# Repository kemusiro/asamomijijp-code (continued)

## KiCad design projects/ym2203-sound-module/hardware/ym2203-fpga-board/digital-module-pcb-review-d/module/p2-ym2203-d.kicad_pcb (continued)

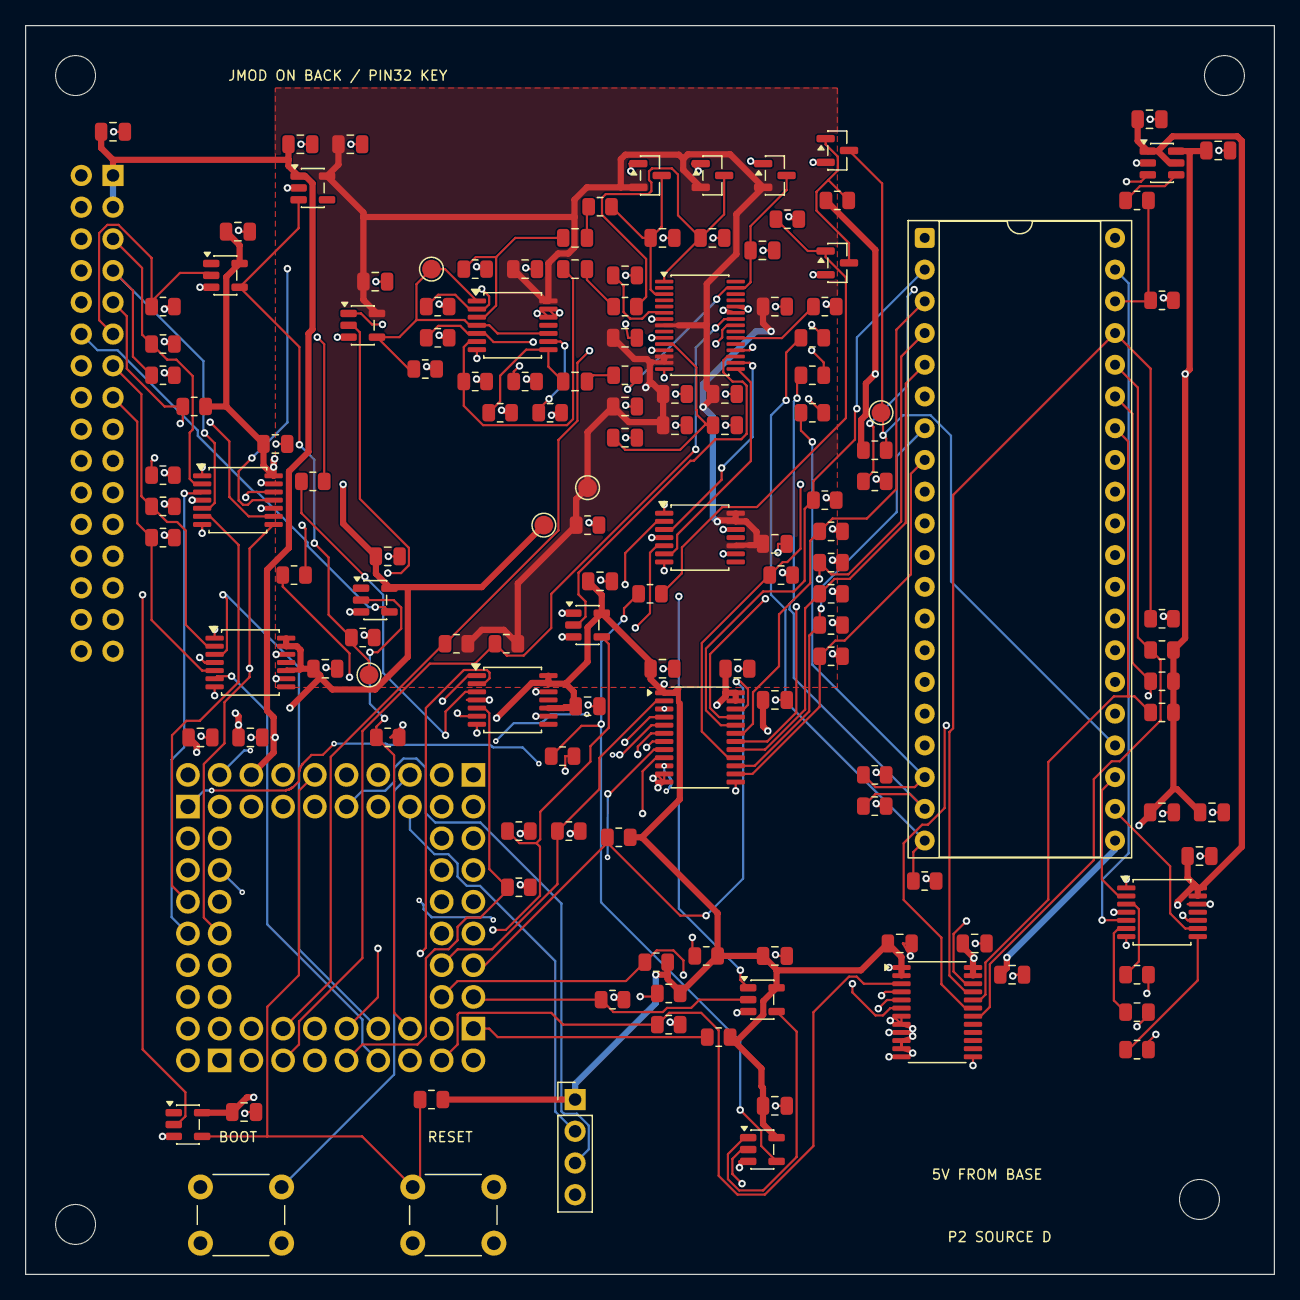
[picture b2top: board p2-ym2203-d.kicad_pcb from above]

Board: 4 copper layers, 100.0 x 100.0 mm, 149 parts (1 on the bottom side), 100 nets.

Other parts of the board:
H1, H2, H3, H4: MountingHole_3.2mm_M3

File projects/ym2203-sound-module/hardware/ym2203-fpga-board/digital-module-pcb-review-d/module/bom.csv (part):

Reference,Value,Footprint,Sheet,Datasheet,Note
Q1,MMBT3904LT1G,Package_TO_SOT_SMD:SOT-23,03-default-reset,https://www.onsemi.com/pdf/datasheet/mmbt3904lt1-d.pdf,
R19,4.7k,Resistor_SMD:R_0805_2012Metric,03-default-reset,,
Q2,MMBT3904LT1G,Package_TO_SOT_SMD:SOT-23,03-default-reset,https://www.onsemi.com/pdf/datasheet/mmbt3904lt1-d.pdf,
R20,10k,Resistor_SMD:R_0805_2012Metric,03-default-reset,,
R21,100k,Resistor_SMD:R_0805_2012Metric,03-default-reset,,
R22,10k,Resistor_SMD:R_0805_2012Metric,03-default-reset,,
R23,100k,Resistor_SMD:R_0805_2012Metric,03-default-reset,,
U8,SN74LVC8T245PWR,Package_SO:TSSOP-24_4.4x7.8mm_P0.65mm,02-level-bus,https://www.ti.com/lit/ds/symlink/sn74lvc8t245.pdf,Bare IC pinout: OE=22 DIR=2; NOT the Rev C breakout numbering
U9,SN74LVC8T245PWR,Package_SO:TSSOP-24_4.4x7.8mm_P0.65mm,02-level-bus,https://www.ti.com/lit/ds/symlink/sn74lvc8t245.pdf,Bare IC pinout: OE=22 DIR=2; NOT the Rev C breakout numbering
C11,100n X7R 10V,Capacitor_SMD:C_0805_2012Metric,02-level-bus,,Capacitor body/height and effective capacitance to be checked against final MPN
C12,100n X7R 10V,Capacitor_SMD:C_0805_2012Metric,02-level-bus,,Capacitor body/height and effective capacitance to be checked against final MPN
C13,100n X7R 10V,Capacitor_SMD:C_0805_2012Metric,02-level-bus,,Capacitor body/height and effective capacitance to be checked against final MPN
C14,100n X7R 10V,Capacitor_SMD:C_0805_2012Metric,02-level-bus,,Capacitor body/height and effective capacitance to be checked against final MPN
C15,100n X7R 10V,Capacitor_SMD:C_0805_2012Metric,02-level-bus,,Capacitor body/height and effective capacitance to be checked against final MPN
C16,100n X7R 10V,Capacitor_SMD:C_0805_2012Metric,02-level-bus,,Capacitor body/height and effective capacitance to be checked against final MPN
RDIR,10k,Resistor_SMD:R_0805_2012Metric,02-level-bus,,
RDOE,10k,Resistor_SMD:R_0805_2012Metric,02-level-bus,,
RCOE,10k,Resistor_SMD:R_0805_2012Metric,02-level-bus,,
RD0,100k,Resistor_SMD:R_0805_2012Metric,02-level-bus,,
RD1,100k,Resistor_SMD:R_0805_2012Metric,02-level-bus,,
RD2,100k,Resistor_SMD:R_0805_2012Metric,02-level-bus,,
RD3,100k,Resistor_SMD:R_0805_2012Metric,02-level-bus,,
RD4,100k,Resistor_SMD:R_0805_2012Metric,02-level-bus,,
RD5,100k,Resistor_SMD:R_0805_2012Metric,02-level-bus,,
RD6,100k,Resistor_SMD:R_0805_2012Metric,02-level-bus,,
RD7,100k,Resistor_SMD:R_0805_2012Metric,02-level-bus,,
R32,10k,Resistor_SMD:R_0805_2012Metric,02-level-bus,,
RMC32,10k,Resistor_SMD:R_0805_2012Metric,02-level-bus,,
R33,10k,Resistor_SMD:R_0805_2012Metric,02-level-bus,,
RMC33,10k,Resistor_SMD:R_0805_2012Metric,02-level-bus,,
R34,10k,Resistor_SMD:R_0805_2012Metric,02-level-bus,,
RMC34,10k,Resistor_SMD:R_0805_2012Metric,02-level-bus,,
R35,100k,Resistor_SMD:R_0805_2012Metric,02-level-bus,,
RMA,100k,Resistor_SMD:R_0805_2012Metric,02-level-bus,,
U12,YM2203C SOCKET,Package_DIP:DIP-40_W15.24mm_Socket,04-ym-fm-clock,https://www.bitsavers.org/components/yamaha/YM2203_198911.pdf,IO ports A/B unused; IRQ unconnected; 5V supply
C19,100n X7R 10V,Capacitor_SMD:C_0805_2012Metric,04-ym-fm-clock,,Capacitor body/height and effective capacitance to be checked against final MPN
C20,10u 10V,Capacitor_SMD:C_0805_2012Metric,04-ym-fm-clock,,Capacitor body/height and effective capacitance to be checked against final MPN
U14,SN74LVC1T45DBVR,Package_TO_SOT_SMD:SOT-23-6,04-ym-fm-clock,https://www.ti.com/lit/ds/symlink/sn74lvc1t45.pdf,Fixed A->B; clock may run while YM RESET is asserted
C23,100n X7R 10V,Capacitor_SMD:C_0805_2012Metric,04-ym-fm-clock,,Capacitor body/height and effective capacitance to be checked against final MPN
C24,100n X7R 10V,Capacitor_SMD:C_0805_2012Metric,04-ym-fm-clock,,Capacitor body/height and effective capacitance to be checked against final MPN
R39,33,Resistor_SMD:R_0805_2012Metric,04-ym-fm-clock,,
R40,100k,Resistor_SMD:R_0805_2012Metric,04-ym-fm-clock,,
U16,SN74LV4T125PWR,Package_SO:TSSOP-14_4.4x5mm_P0.65mm,04-ym-fm-clock,https://www.ti.com/lit/ds/symlink/sn74lv4t125.pdf,"Ioff5V YM receiver, local3V3. Third output isSH, not LRCK."
C27,100n X7R 10V,Capacitor_SMD:C_0805_2012Metric,04-ym-fm-clock,,Capacitor body/height and effective capacitance to be checked against final MPN
RL0,1.33k 1%,Resistor_SMD:R_0805_2012Metric,05-ssg,,
RL1,1.33k 1%,Resistor_SMD:R_0805_2012Metric,05-ssg,,
RL2,1.33k 1%,Resistor_SMD:R_0805_2012Metric,05-ssg,,
RS3,33,Resistor_SMD:R_0805_2012Metric,04-ym-fm-clock,,
RS6,33,Resistor_SMD:R_0805_2012Metric,04-ym-fm-clock,,
RS8,33,Resistor_SMD:R_0805_2012Metric,04-ym-fm-clock,,
JCORE1,Core2350B0 P1 SOCKET,P2D:Core2350B0_P1_IndividualSockets,02-core,https://files.waveshare.com/wiki/Core2350B0/Core2350B.pdf,Logical16-contact group; physical16individual receptacles. Not a rectangular2x08 socket. See ASSEMBLY.md.
JCORE2,Core2350B0 P2 SOCKET,P2D:Core2350B0_P2_IndividualSockets,02-core,https://files.waveshare.com/wiki/Core2350B0/Core2350B.pdf,Logical16-contact group; physical16individual receptacles. Not a rectangular2x08 socket. See ASSEMBLY.md.
JCORE3,Core2350B0 P3 SOCKET,P2D:Core2350B0_P3_IndividualSockets,02-core,https://files.waveshare.com/wiki/Core2350B0/Core2350B.pdf,Logical16-contact group; physical16individual receptacles. Not a rectangular2x08 socket. See ASSEMBLY.md.
JCORE4,Core2350B0 P4 SOCKET,P2D:Core2350B0_P4_IndividualSockets,02-core,https://files.waveshare.com/wiki/Core2350B0/Core2350B.pdf,Logical16-contact group; physical16individual receptacles. Not a rectangular2x08 socket. See ASSEMBLY.md.
CCORE,100n X7R 10V,Capacitor_SMD:C_0805_2012Metric,02-core,,
CCOREB,4.7u X7R 10V,Capacitor_SMD:C_0805_2012Metric,02-core,,
JSWD,Core SWD / VREF input only,Connector_PinHeader_2.54mm:PinHeader_1x04_P2.54mm_Vertical,02-core,,Probe VREF is sense only; carrier supplies power. Do not connect moduleUSB adapter VBUS simultaneously.
SWCOREBOOT,SWCOREBOOT,Button_Switch_THT:SW_PUSH_6mm_H4.3mm,02-core,,
SWCORERESET,SWCORERESET,Button_Switch_THT:SW_PUSH_6mm_H4.3mm,02-core,,
UENABLE,SN74LVC1G17DBVR,Package_TO_SOT_SMD:SOT-23-5,03-default-reset,https://www.ti.com/lit/ds/symlink/sn74lvc1g17.pdf,
URUNOD,SN74LVC1G07DBVR,Package_TO_SOT_SMD:SOT-23-5,03-default-reset,https://www.ti.com/lit/ds/symlink/sn74lvc1g07.pdf,
UYMALLOW,SN74LVC1G08DBVR,Package_TO_SOT_SMD:SOT-23-5,03-default-reset,https://www.ti.com/lit/ds/symlink/sn74lvc1g08.pdf,
CUENABLE,100n X7R 10V,Capacitor_SMD:C_0805_2012Metric,03-default-reset,,
CURUNOD,100n X7R 10V,Capacitor_SMD:C_0805_2012Metric,03-default-reset,,
CUYMALLOW,100n X7R 10V,Capacitor_SMD:C_0805_2012Metric,03-default-reset,,
RENPD,10k,Resistor_SMD:R_0805_2012Metric,03-default-reset,,
RRUNUP,10k,Resistor_SMD:R_0805_2012Metric,03-default-reset,,
RADENPD,10k,Resistor_SMD:R_0805_2012Metric,03-default-reset,,
UYMRUN,SN74LVC1G08DBVR,Package_TO_SOT_SMD:SOT-23-5,03-default-reset,https://www.ti.com/lit/ds/symlink/sn74lvc1g08.pdf,
CUYMRUN,100n X7R 10V,Capacitor_SMD:C_0805_2012Metric,03-default-reset,,
RYMSAFEPD,100k,Resistor_SMD:R_0805_2012Metric,03-default-reset,,
ULINK0,SN74LV4T125PWR,Package_SO:TSSOP-14_4.4x5mm_P0.65mm,01-link,https://www.ti.com/lit/ds/symlink/sn74lv4t125.pdf,Ioff receiver rail; input defaults explicit; unused gates disabled; NOT plainLVC125A
ULINK1,SN74LV4T125PWR,Package_SO:TSSOP-14_4.4x5mm_P0.65mm,01-link,https://www.ti.com/lit/ds/symlink/sn74lv4t125.pdf,Ioff receiver rail; input defaults explicit; unused gates disabled; NOT plainLVC125A
ULINKTX,SN74LV4T125PWR,Package_SO:TSSOP-14_4.4x5mm_P0.65mm,01-link,https://www.ti.com/lit/ds/symlink/sn74lv4t125.pdf,Ioff receiver rail; input defaults explicit; unused gates disabled; NOT plainLVC125A
CULINK0,100n X7R 10V,Capacitor_SMD:C_0805_2012Metric,01-link,,
CULINK1,100n X7R 10V,Capacitor_SMD:C_0805_2012Metric,01-link,,
CULINKTX,100n X7R 10V,Capacitor_SMD:C_0805_2012Metric,01-link,,
RMSCK,100k,Resistor_SMD:R_0805_2012Metric,01-link,,
RMMOSI,100k,Resistor_SMD:R_0805_2012Metric,01-link,,
RMCS,10k,Resistor_SMD:R_0805_2012Metric,01-link,,
RMBCK,100k,Resistor_SMD:R_0805_2012Metric,01-link,,
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
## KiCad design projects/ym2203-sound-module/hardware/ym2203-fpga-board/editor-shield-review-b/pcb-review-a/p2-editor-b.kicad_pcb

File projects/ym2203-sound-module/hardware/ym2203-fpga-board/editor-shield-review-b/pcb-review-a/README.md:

# 音色編集シールド review B — PCB review A

2026-11-18。秋月採用品を使ったreview B回路を配置・配線した**2層、76×100mmの試作候補**。
ベースreview Iと重ねるためクロックDIPの窓、ベースSTOPとTESTの切欠きを設けた。
製造発注・実物嵌合・P2 firmware実装・実機受入はまだ行っていない。

| 対象 | 結果 |
| --- | --- |
| 電気部品 / 物理pad | 46参照 / 159pad（取付穴7個を含め166pad） |
| 配線 | 692 segment、28 via、最小幅0.25mm、表裏GND面 |
| ERC / DRC / 未配線 / 回路図差分 | **0 / 0 / 0 / 0** |
| DRC個別除外 | 0。ベースIと同じKiCad既定ignore5項目は[検証記録](verification.json)に列記 |
| UNO嵌合 | 裏面雄32接点、ベースIの同番号座標と全点一致 |
| メモリー等のPCモデル | 親review Bの13試験は合格、実EEPROMの試験ではない |

編集可能な[配線済みPCB](p2-editor-b.kicad_pcb)と[回路図](p2-editor-b.kicad_sch)がCAD正本。
[表面銅箔](preview-top.svg)・[裏面銅箔](preview-bottom.svg)、[配置表](placement.csv)、
[パッド照合](native-pads.json)、[機構・電源・組立条件](ASSEMBLY.md)も参照する。

## 部品と機構

- 秋月LCD M154、B10k×4、RE111F、EEPROM、ボタンを維持。Waveshare販売品も選定可とする。
  今回の配置には秋月品で解消できない干渉はなかったため、供給元を変える目的だけの交換はしていない。
- LCDは横向き・コネクタを左へ向け、12mmの絶縁支持で持ち上げる。エンコーダー軸の上へケーブルを通さない。
- つまみは外径16mm、19mm間隔。軸位置の相対許容を各0.5mm置いても隙間2mm。
- エンコーダーの位置決め穴は、図面の長穴を反映して2.1×1.6mmとした。中心穴は2.15mm。
- UNOの裏面雄ヘッダーを、上から見た座標でベースと照合。ICSPには嵌合せず、上方にTHTリードを置かない。
- 支持はUNOの3か所とLCDの4か所。音源基板とのXY間隔は7mmを維持する。

ベースIのCore2350B0はWaveshare品を想定したままで、モジュールやそのGPIOは変更しない。
最新購入ロットのUSB/FPC・ピン長・ソケットの現物嵌合は、元のベースIと同様に未受入。
LCDだけでなく、ソケット・支持材と長いボリューム軸の確認を[組立手順](ASSEMBLY.md)に残した。

## 互換性と検証範囲

review Bの46参照の値・footprint識別子・pin/netを維持する。PCB用のED2ライブラリでは
裏面ヘッダーを正しい座標で定義し、エンコーダーの長穴と取付穴を追加した。
親review Bの回路図とライブラリは当時の候補記録として保存し、このディレクトリのライブラリをPCBに用いる。

ベースI/H、40接点、HOST/player、C firmwareは変更しない。
I2C0x42/100kHz、既存WYM1・PUSH32・FIFO1024・1000ms lease、USB-MIDI/CDC所有権とglobal STOPを維持する設計契約。
シールドD0のSTOPはP2 firmwareでglobal STOPへ接続する必要があり、独立したハード停止回路ではない。
**新PCBでHOST・USB-MIDI・停止が動作したという実機合格ではない。**

## 再検証

KiCad10.0.5、pcbnew付属Python3.9.13。以下のpython3はpcbnewを使えるものを指定する。[ツール・来歴](toolchain.json)。

```sh
python3 validate.py  # ERC・DRCを実行し、保存CADとレポートのSHA-256を結び付ける
# KiCad pcbnewを使えるPythonで、結果を上書きせず照合する
python3 verify.py
# レポートの更新を伴う検証
python3 verify.py --write
# 親ディレクトリの音色・EEPROM計画モデル
cd ..
python3 -m unittest -v
```

`build_pcb.py`は初期配置の参考生成器。最終配線を再現するものではない。
生成途中のplaced/DSN/SESやルーター環境は配布しない。最終の修正配線・GND面・サーマルはnative PCBが正本。
回路変更時は、この回路図と親review Bの回路正本との一致も保ち、ERC・DRC・`verify.py`を再実行する。

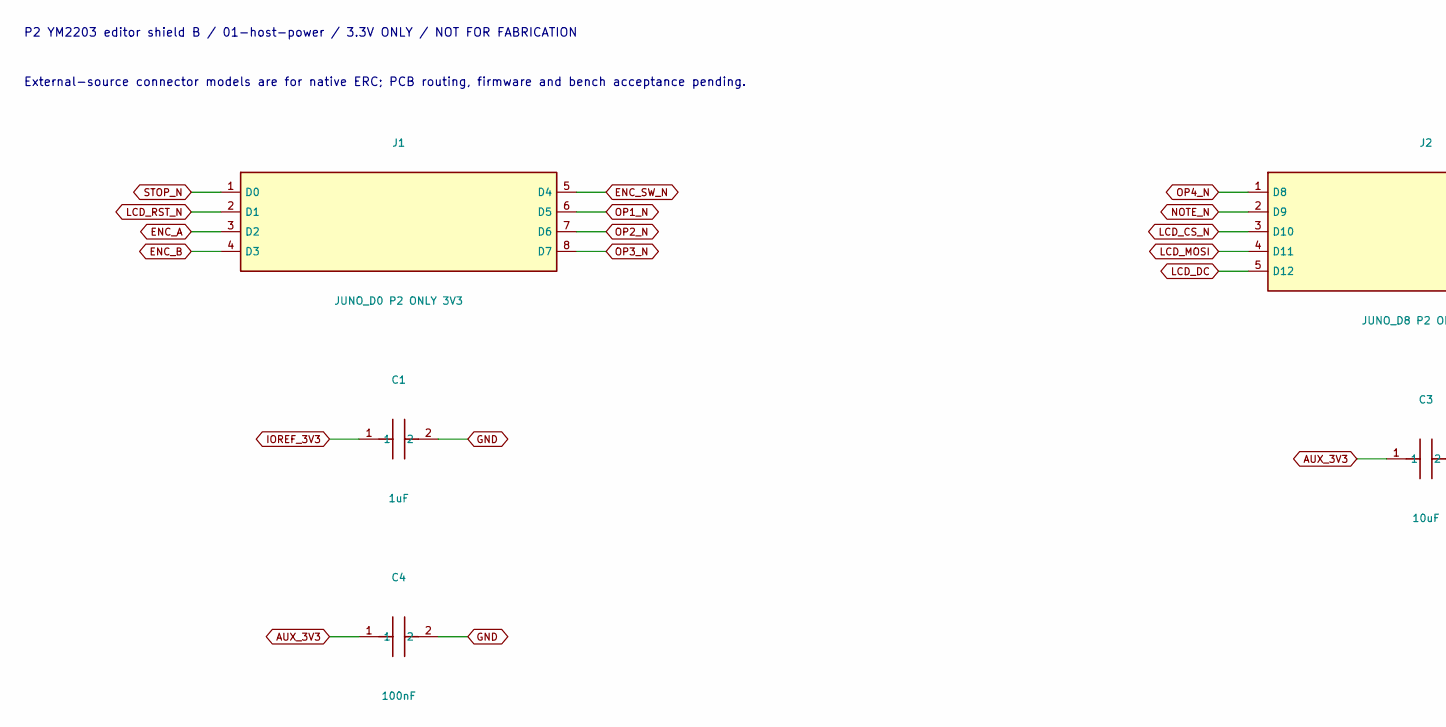
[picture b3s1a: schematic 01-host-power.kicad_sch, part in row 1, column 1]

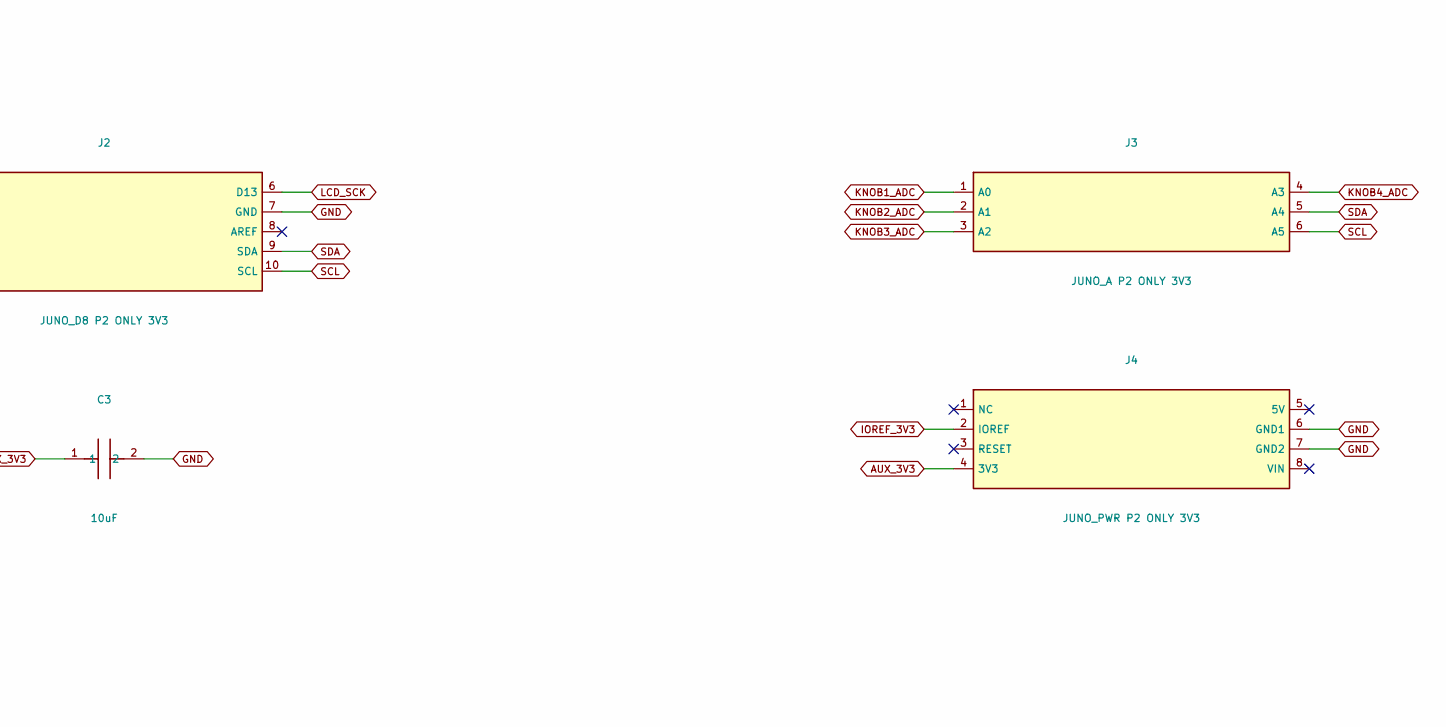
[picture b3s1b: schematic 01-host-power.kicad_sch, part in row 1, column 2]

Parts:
C1: 1uF; C_0805_2012Metric
C3: 10uF; C_0805_2012Metric
C4: 100nF; C_RDE_100n_P2_5
J1: JUNO_D0 P2 ONLY 3V3; JUNO_D0
J2: JUNO_D8 P2 ONLY 3V3; JUNO_D8
J3: JUNO_A P2 ONLY 3V3; JUNO_A
J4: JUNO_PWR P2 ONLY 3V3; JUNO_PWR

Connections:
AUX_3V3: C3.1, C4.1, J4.4 (3V3); also elsewhere on the board
ENC_A: J1.3 (D2); also elsewhere on the board
ENC_B: J1.4 (D3); also elsewhere on the board
ENC_SW_N: J1.5 (D4); also elsewhere on the board
GND: C1.2, C3.2, C4.2, J2.7 (GND), J4.6 (GND1), J4.7 (GND2); also elsewhere on the board
IOREF_3V3: C1.1, J4.2 (IOREF); also elsewhere on the board
KNOB1_ADC: J3.1 (A0); also elsewhere on the board
KNOB2_ADC: J3.2 (A1); also elsewhere on the board
KNOB3_ADC: J3.3 (A2); also elsewhere on the board
KNOB4_ADC: J3.4 (A3); also elsewhere on the board
LCD_CS_N: J2.3 (D10); also elsewhere on the board
LCD_DC: J2.5 (D12); also elsewhere on the board
LCD_MOSI: J2.4 (D11); also elsewhere on the board
LCD_RST_N: J1.2 (D1); also elsewhere on the board
LCD_SCK: J2.6 (D13); also elsewhere on the board
NOTE_N: J2.2 (D9); also elsewhere on the board
OP1_N: J1.6 (D5); also elsewhere on the board
OP2_N: J1.7 (D6); also elsewhere on the board
OP3_N: J1.8 (D7); also elsewhere on the board
OP4_N: J2.1 (D8); also elsewhere on the board
SCL: J2.10 (SCL), J3.6 (A5); also elsewhere on the board
SDA: J2.9 (SDA), J3.5 (A4); also elsewhere on the board
STOP_N: J1.1 (D0); also elsewhere on the board

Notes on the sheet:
P2 YM2203 editor shield B / 01-host-power / 3.3V ONLY / NOT FOR FABRICATION
External-source connector models are for native ERC; PCB routing, firmware and bench acceptance pending.

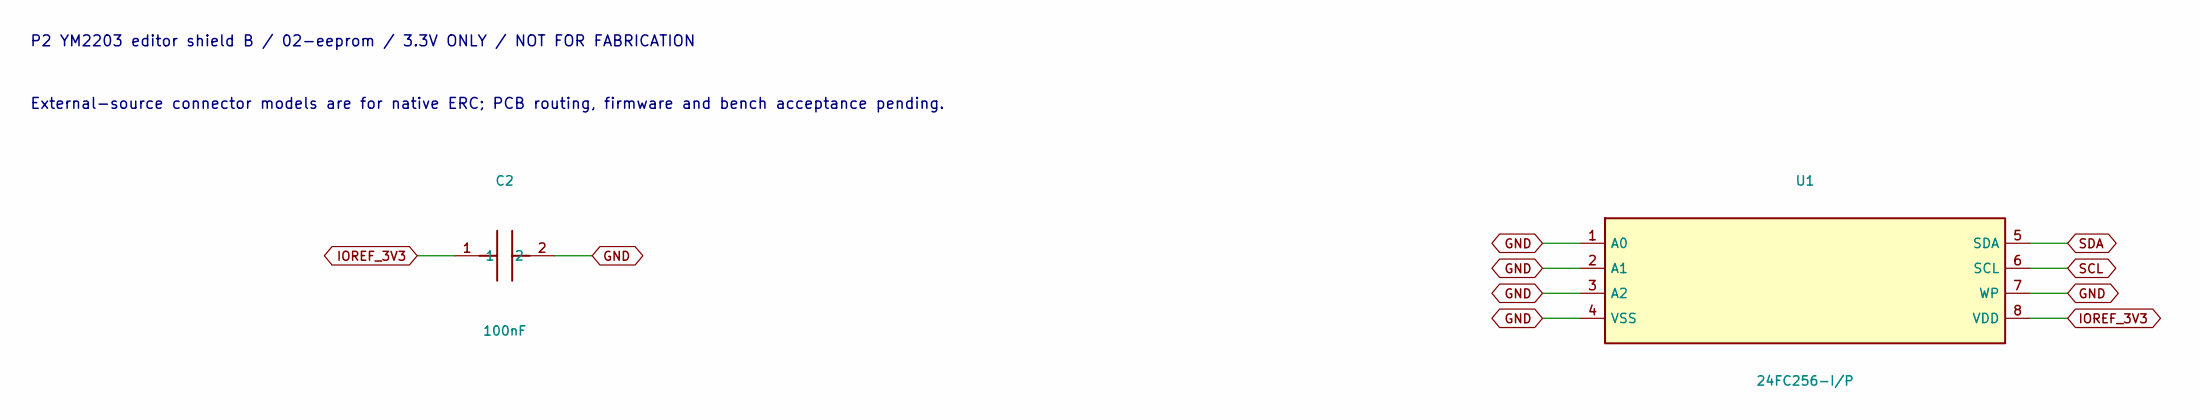
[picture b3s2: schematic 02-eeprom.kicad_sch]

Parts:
C2: 100nF; C_RDE_100n_P2_5
U1: 24FC256-I/P; DIP-8_W7.62mm

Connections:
GND: C2.2, U1.1 (A0), U1.2 (A1), U1.3 (A2), U1.4 (VSS), U1.7 (WP); also elsewhere on the board
IOREF_3V3: C2.1, U1.8 (VDD); also elsewhere on the board
SCL: U1.6 (SCL); also elsewhere on the board
SDA: U1.5 (SDA); also elsewhere on the board

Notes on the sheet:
P2 YM2203 editor shield B / 02-eeprom / 3.3V ONLY / NOT FOR FABRICATION
External-source connector models are for native ERC; PCB routing, firmware and bench acceptance pending.

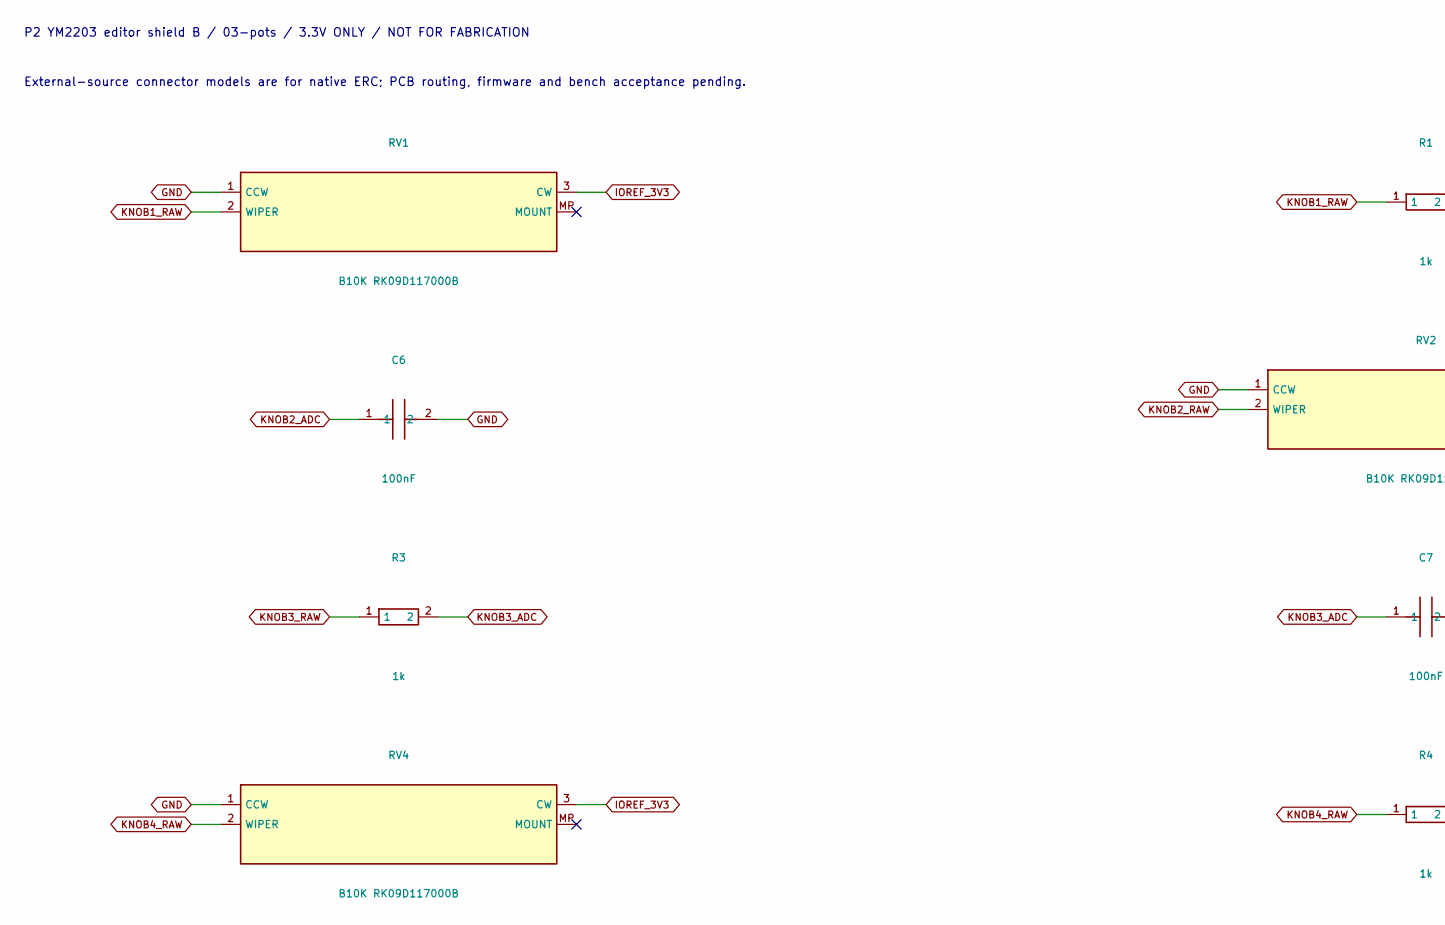
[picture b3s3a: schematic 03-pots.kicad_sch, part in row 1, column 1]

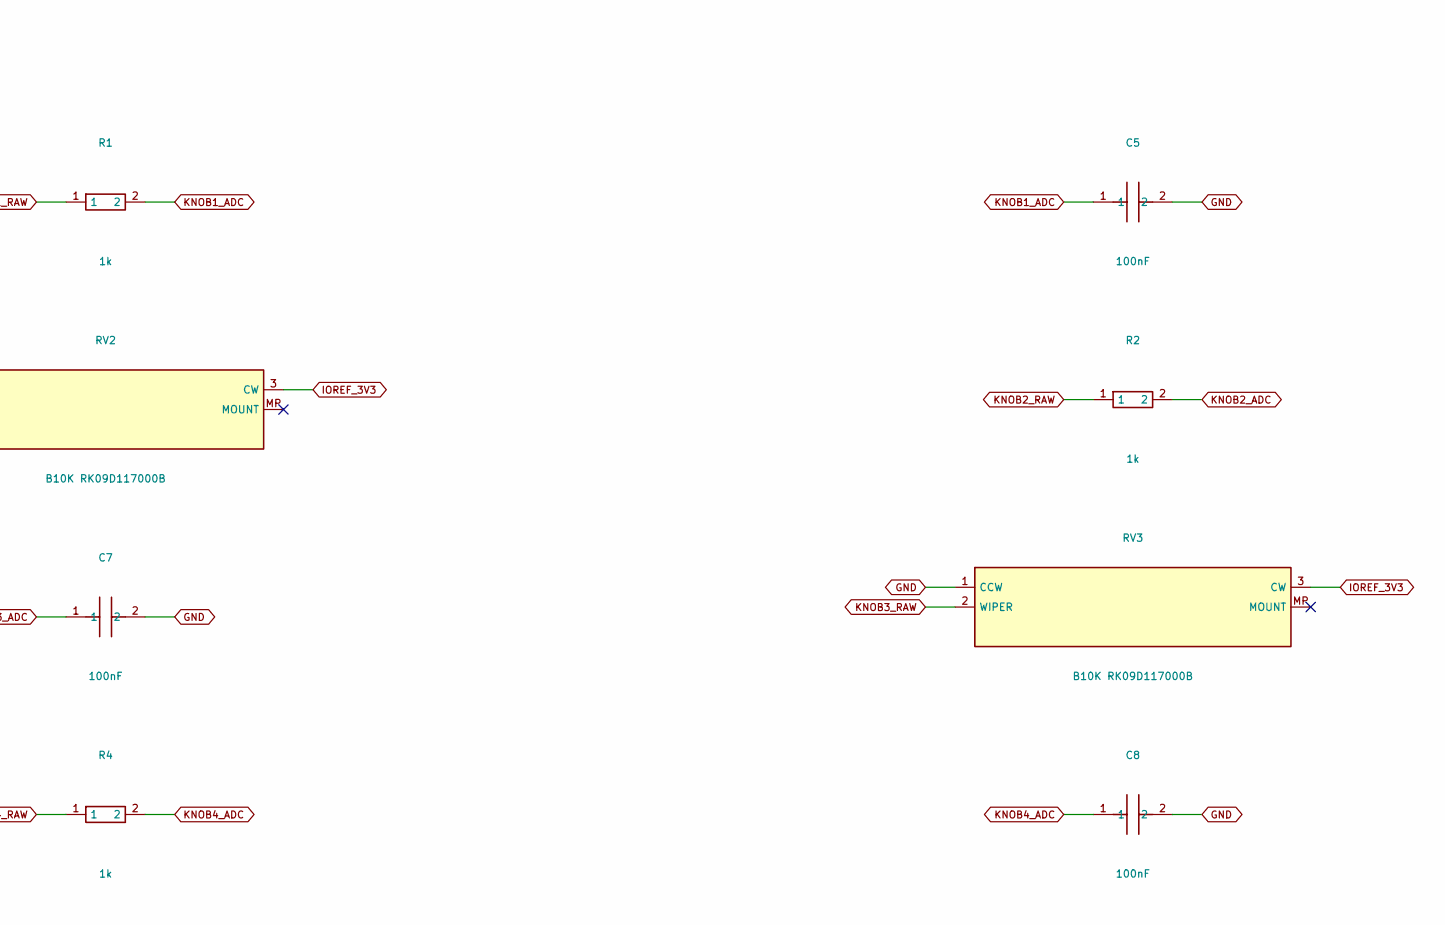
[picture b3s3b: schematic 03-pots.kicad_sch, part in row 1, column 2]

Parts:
C5, C6, C7, C8: 100nF; C_RDE_100n_P2_5
R1, R2, R3, R4: 1k; R_Axial_DIN0204_L3.6mm_D1.6mm_P7.62mm_Horizontal
RV1, RV2, RV3, RV4: B10K RK09D117000B; Potentiometer_Alps_RK09K_Single_Vertical

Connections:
GND: C5.2, C6.2, C7.2, C8.2, RV1.1 (CCW), RV2.1 (CCW), RV3.1 (CCW), RV4.1 (CCW); also elsewhere on the board
IOREF_3V3: RV1.3 (CW), RV2.3 (CW), RV3.3 (CW), RV4.3 (CW); also elsewhere on the board
KNOB1_ADC: C5.1, R1.2; also elsewhere on the board
KNOB1_RAW: R1.1, RV1.2 (WIPER)
KNOB2_ADC: C6.1, R2.2; also elsewhere on the board
KNOB2_RAW: R2.1, RV2.2 (WIPER)
KNOB3_ADC: C7.1, R3.2; also elsewhere on the board
KNOB3_RAW: R3.1, RV3.2 (WIPER)
KNOB4_ADC: C8.1, R4.2; also elsewhere on the board
KNOB4_RAW: R4.1, RV4.2 (WIPER)

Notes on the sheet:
P2 YM2203 editor shield B / 03-pots / 3.3V ONLY / NOT FOR FABRICATION
External-source connector models are for native ERC; PCB routing, firmware and bench acceptance pending.

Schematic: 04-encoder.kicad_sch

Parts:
C9, C10: 10nF; C_RDE_10n_P5
ENC1: ALPHA RE111F-4S1-152S4-15P-A; RE111F_4S1_ReviewB
R5, R7: 2.7k; R_Axial_DIN0204_L3.6mm_D1.6mm_P7.62mm_Horizontal
R6, R8: 1k; R_Axial_DIN0204_L3.6mm_D1.6mm_P7.62mm_Horizontal
R9: 4.7k; R_Axial_DIN0204_L3.6mm_D1.6mm_P7.62mm_Horizontal

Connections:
ENC_A: C9.1, R6.2; also elsewhere on the board
ENC_A_CONTACT: ENC1.A, R5.2, R6.1
ENC_B: C10.1, R8.2; also elsewhere on the board
ENC_B_CONTACT: ENC1.B, R7.2, R8.1
ENC_SW_N: ENC1.S1 (SW), R9.2; also elsewhere on the board
GND: C9.2, C10.2, ENC1.C (COM), ENC1.S2 (SW_COM); also elsewhere on the board
IOREF_3V3: R5.1, R7.1, R9.1; also elsewhere on the board

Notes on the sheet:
P2 YM2203 editor shield B / 04-encoder / 3.3V ONLY / NOT FOR FABRICATION
External-source connector models are for native ERC; PCB routing, firmware and bench acceptance pending.

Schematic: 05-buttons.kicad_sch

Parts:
R10, R11, R12, R13, R14, R15: 10k; R_Axial_DIN0204_L3.6mm_D1.6mm_P7.62mm_Horizontal
SW1: OP1 TVDP01-095BB1; SW_PUSH_6mm_H9.5mm
SW2: OP2 TVDP01-095BB1; SW_PUSH_6mm_H9.5mm
SW3: OP3 TVDP01-095BB1; SW_PUSH_6mm_H9.5mm
SW4: OP4 TVDP01-095BB1; SW_PUSH_6mm_H9.5mm
SW5: NOTE TVDP01-095BB1; SW_PUSH_6mm_H9.5mm
SW6: STOP TVDP01-095BB1; SW_PUSH_6mm_H9.5mm

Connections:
GND: SW1.2 (COM), SW2.2 (COM), SW3.2 (COM), SW4.2 (COM), SW5.2 (COM), SW6.2 (COM); also elsewhere on the board
IOREF_3V3: R10.1, R11.1, R12.1, R13.1, R14.1, R15.1; also elsewhere on the board
NOTE_N: R14.2, SW5.1 (NO); also elsewhere on the board
OP1_N: R10.2, SW1.1 (NO); also elsewhere on the board
OP2_N: R11.2, SW2.1 (NO); also elsewhere on the board
OP3_N: R12.2, SW3.1 (NO); also elsewhere on the board
OP4_N: R13.2, SW4.1 (NO); also elsewhere on the board
STOP_N: R15.2, SW6.1 (NO); also elsewhere on the board

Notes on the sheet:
P2 YM2203 editor shield B / 05-buttons / 3.3V ONLY / NOT FOR FABRICATION
External-source connector models are for native ERC; PCB routing, firmware and bench acceptance pending.

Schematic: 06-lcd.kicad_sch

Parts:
J5: M154-240240-RGB 20261020 cable; PinHeader_1x08_P2.54mm_Vertical
R16, R17: 10k; R_Axial_DIN0204_L3.6mm_D1.6mm_P7.62mm_Horizontal
R18, R19: 33; R_Axial_DIN0204_L3.6mm_D1.6mm_P7.62mm_Horizontal

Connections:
AUX_3V3: J5.2 (VCC), J5.8 (BLK); also elsewhere on the board
GND: J5.1 (GND); also elsewhere on the board
IOREF_3V3: R16.1, R17.1; also elsewhere on the board
LCD_CLK_OUT: J5.3 (SCL_SPI), R18.2
LCD_CS_N: J5.7 (CS), R16.2; also elsewhere on the board
LCD_DC: J5.6 (DC); also elsewhere on the board
LCD_DIN_OUT: J5.4 (SDA_SPI), R19.2
LCD_MOSI: R19.1; also elsewhere on the board
LCD_RST_N: J5.5 (RES), R17.2; also elsewhere on the board
LCD_SCK: R18.1; also elsewhere on the board

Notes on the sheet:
P2 YM2203 editor shield B / 06-lcd / 3.3V ONLY / NOT FOR FABRICATION
External-source connector models are for native ERC; PCB routing, firmware and bench acceptance pending.

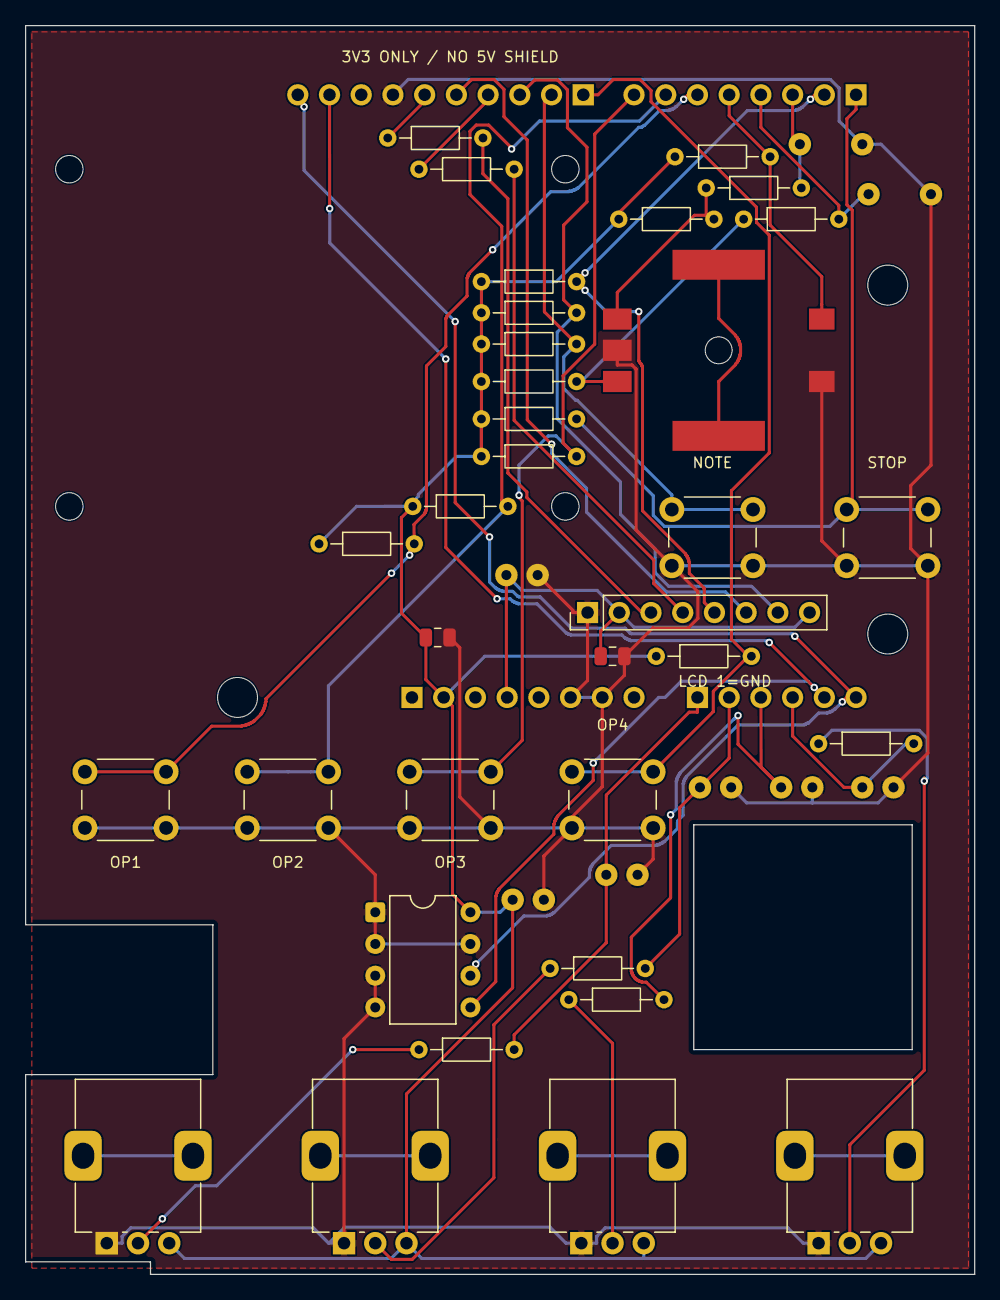
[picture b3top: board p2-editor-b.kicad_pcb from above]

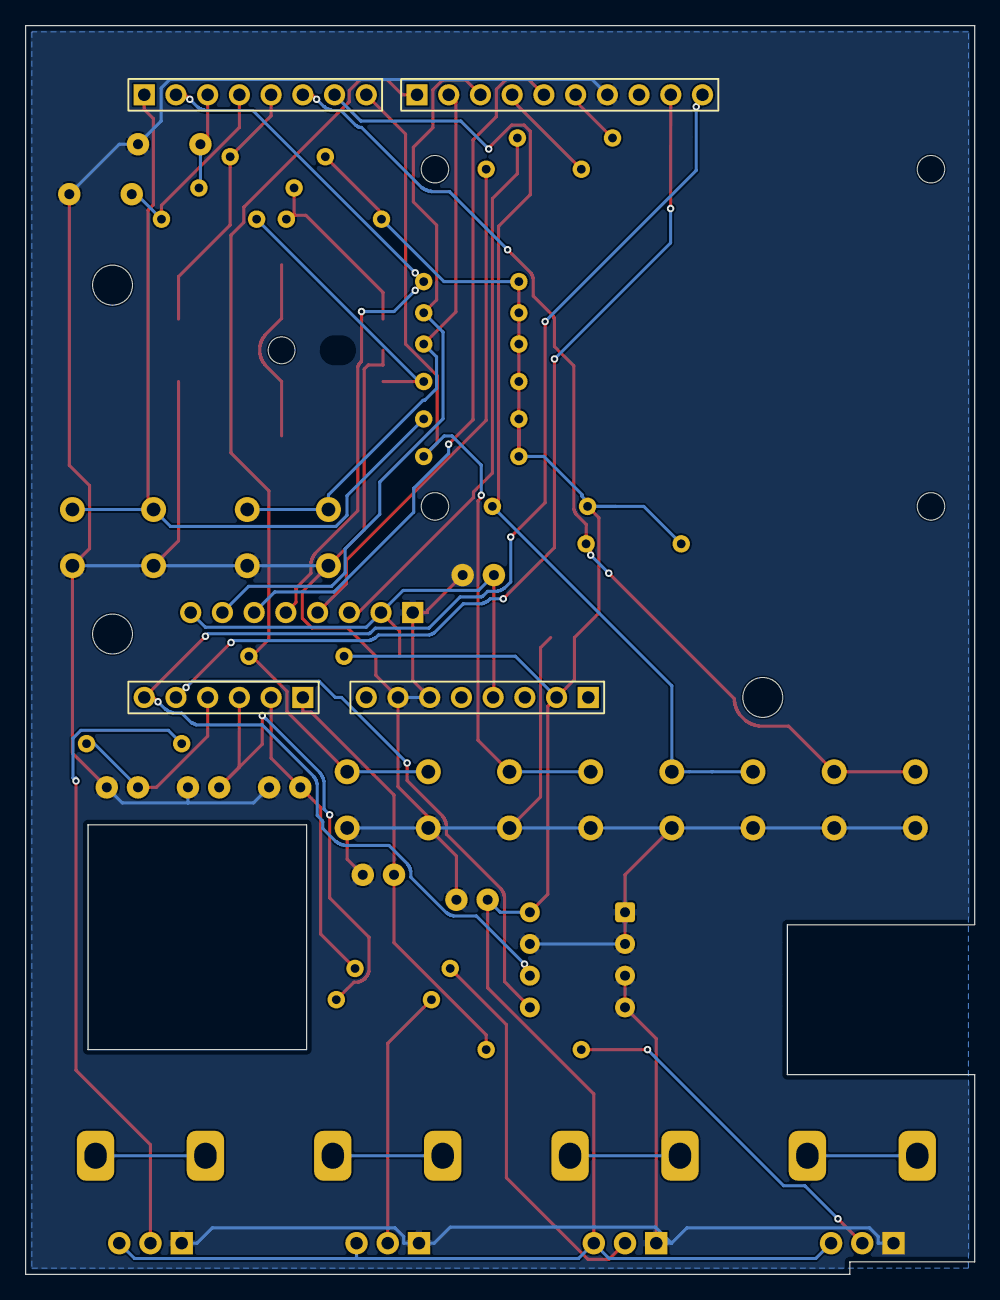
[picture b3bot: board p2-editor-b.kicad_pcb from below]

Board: 2 copper layers, 76.0 x 100.0 mm, 53 parts (4 on the bottom side), 31 nets.

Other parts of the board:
H1, H2, H3: M3 UNO support; M3_UNO
HL1, HL2, HL3, HL4: M2 LCD support; M2_LCD
